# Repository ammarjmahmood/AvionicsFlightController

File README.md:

# Avionics Flight Controller - Hello Kitty PCB Outline

<div align="center">
 
</div>

## Project Overview

This repository contains KiCad PCB designs for avionics flight controllers specifically designed for model rockets. The project aims to develop and deploy over 20 flight controller systems for rocket launches scheduled for May 2026.

Our avionics system consists of a three stack board design:

1. **GPS Board** (Currently Available)
2. **Sensor Board** (Coming Soon)
3. **Power Board** (Coming Soon)

## Current Progress

The GPS board design is now complete and ready for review. This board handles positioning data for the rocket during flight and recovery phases.

## Upcoming Work

Work is ongoing for the sensor and power boards which will complete the Hello Kitty avionics stack:

* **Sensor Board**: Will incorporate accelerometers, gyroscopes, barometers, and other sensors necessary for flight data collection
* **Power Board**: Will manage power distribution, battery management, and charging systems

## Project Timeline

* **2025 Q2**: GPS Board design and testing
* **2025 Q3**: Sensor Board design
* **2025 Q4**: Power Board design
* **2026 Q1**: Integration testing and flight preparation
* **2026 May**: Launch of 20+ rockets with Hello Kitty avionics systems

## Contributing

We welcome contributions to this project! If you have experience with PCB design, embedded systems, or rocket avionics, your input is valuable to us.

Some ways you can contribute:
* Review existing designs and suggest improvements
* Help with electrical schematics
* Assist with component selection for optimal performance
* Contribute to firmware development
* Share your experience with similar avionics systems

## Advice for Contributors

When contributing to this project, keep in mind:

* All designs should maintain compatibility with the three stack system
* Power consumption is a critical consideration
* Size and weight constraints are important for flight performance
* Robustness is essential for surviving launch conditions

## License

MIT License
Copyright (c) 2025
Permission is hereby granted, free of charge, to any person obtaining a copy
of this software and associated documentation files (the "Software"), to deal
in the Software without restriction, including without limitation the rights
to use, copy, modify, merge, publish, distribute, sublicense, and/or sell
copies of the Software, and to permit persons to whom the Software is
furnished to do so, subject to the following conditions:
The above copyright notice and this permission notice shall be included in all
copies or substantial portions of the Software.
THE SOFTWARE IS PROVIDED "AS IS", WITHOUT WARRANTY OF ANY KIND, EXPRESS OR
IMPLIED, INCLUDING BUT NOT LIMITED TO THE WARRANTIES OF MERCHANTABILITY,
FITNESS FOR A PARTICULAR PURPOSE AND NONINFRINGEMENT. IN NO EVENT SHALL THE
AUTHORS OR COPYRIGHT HOLDERS BE LIABLE FOR ANY CLAIM, DAMAGES OR OTHER
LIABILITY, WHETHER IN AN ACTION OF CONTRACT, TORT OR OTHERWISE, ARISING FROM,
OUT OF OR IN CONNECTION WITH THE SOFTWARE OR THE USE OR OTHER DEALINGS IN THE
SOFTWARE.

## Contact

Contact
Please reach out via LinkedIn for questions or collaboration opportunities.

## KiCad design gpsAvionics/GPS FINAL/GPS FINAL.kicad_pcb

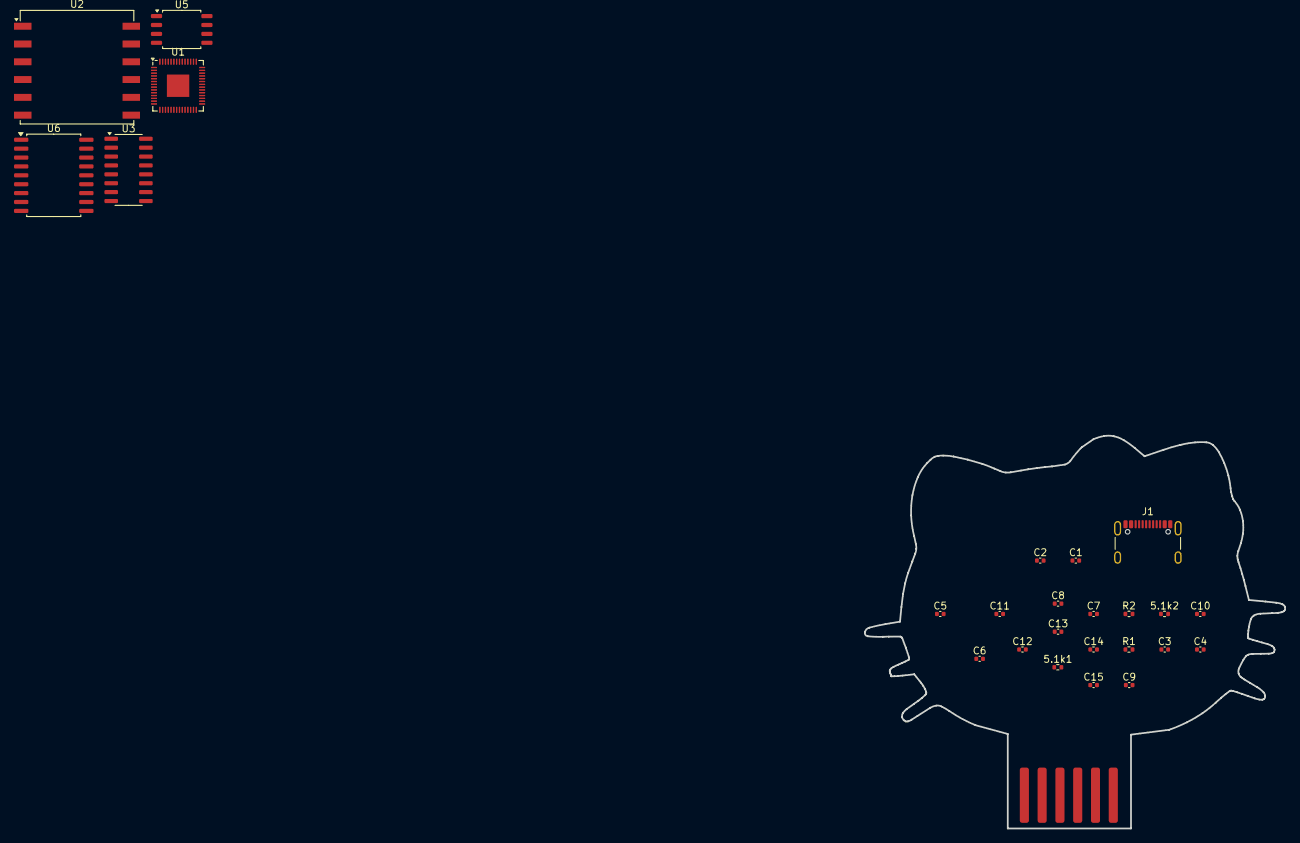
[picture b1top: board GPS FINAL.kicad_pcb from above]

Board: 2 copper layers, 60.0 x 56.1 mm, 25 parts (0 on the bottom side), 25 nets, no tracks yet.

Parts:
5.1k1, 5.1k2: 5.1k; R_0402_1005Metric
C1, C2, C3, C4: 22pF; C_0402_1005Metric
C5, C6, C7, C8, C9, C10, C12, C13, C14, C15: 100nF; C_0402_1005Metric
C11: 1.0pf; C_0402_1005Metric
J1: USB C; USB_C_Receptacle_GCT_USB4105-xx-A_16P_TopMnt_Horizontal
R1: 5.1k; R_0402_1005Metric
R2: 27.4K; R_0402_1005Metric
U1: RP2040; QFN-56-1EP_7x7mm_P0.4mm_EP3.2x3.2mm
U2: L80-R; Quectel_L80-R
U3: CH340G; SOIC-16_3.9x9.9mm_P1.27mm
U5: W25Q128JVS; SOIC-8_5.23x5.23mm_P1.27mm
U6: MCP2515-xSO; SOIC-18W_7.5x11.6mm_P1.27mm

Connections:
+1V1: C13.1, C14.1, C15.2, U1.23 (DVDD), U1.45 (VREG_VOUT), U1.50 (DVDD)
+3.3V: C5.2, C6.2, C7.2, C8.2, C9.2, C10.2, C11.2, C12.2, U1.1 (IOVDD), U1.10 (IOVDD), U1.22 (IOVDD), U1.33 (IOVDD), U1.42 (IOVDD), U1.43 (ADC_AVDD), U1.44 (VREG_IN), U1.48 (USB_VDD), U1.49 (IOVDD)
/3V3: U2.4 (VCC), U3.16 (VCC), U5.8 (VCC)
/CAN_INT: U1.8 (GPIO6), U6.12 (~INT)
/CH340G XO: C4.1, U3.8 (XO)
/CH340G_XI: C3.1, U3.7 (XI)
/NRESET: U1.26 (RUN), U3.13 (~DTR)
/QSPI_CLK: U1.52 (QSPI_SCLK), U5.6 (CLK)
/QSPI_IO0: U1.53 (QSPI_SD0), U5.5 (DI(IO0))
/QSPI_IO1: U1.55 (QSPI_SD1), U5.2 (DO(IO1))
/QSPI_IO2: U1.54 (QSPI_SD2), U5.3 (IO2)
/QSPI_IO3: U1.51 (QSPI_SD3), U5.7 (IO3)
/SPI0_CS: U1.7 (GPIO5), U6.16 (~CS)
/SPI0_MISO: U1.6 (GPIO4), U6.15 (SO)
/SPI0_MOSI: U1.5 (GPIO3), U6.14 (SI)
/SPI0_SCK: U1.4 (GPIO2), U6.13 (SCK)
/UART0_RX: U1.3 (GPIO1), U2.2 (TXD1), U3.2 (TXD)
/UART0_TX: U1.2 (GPIO0), U2.1 (RXD1), U3.3 (RXD)
/USB_DM: J1.A7 (DN1), J1.B7 (DN2), R2.1, U3.6 (UD-)
/USB_DP: J1.A6 (DP1), J1.B6 (DP2), U3.5 (UD+)
/XIN: C1.1, U1.20 (XIN)
/XOUT: C2.1, U1.21 (XOUT)
Earth: 5.1k1.2, 5.1k2.2, C1.2, C2.2, C3.2, C4.2, C5.1, C6.1, C7.1, C8.1, C9.1, C10.1, C11.1, C12.1, C13.2, C14.2, C15.1, U1.19 (TESTEN), U1.57 (GND), U2.3 (GND), U2.12 (GND), U3.1 (GND), U5.4 (GND)
unnamed: R2.2, U1.46 (USB_DM)
unnamed: R1.2, U1.47 (USB_DP)

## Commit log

2025-04-05 upload files
